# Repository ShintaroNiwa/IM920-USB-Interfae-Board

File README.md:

# IM920c/s/sl USB Interface Board
インタープラン社の無線モジュール、IM920シリーズをUSB Type-CでPCに接続するためのインターフェースボードです。
USBシリアルコンバータICには、部室に余っていたCH340Cを使用します。
対応する無線モジュールについては以下の通りです。
|対応無線モジュール|
|---|
|IM920c|
|IM920s|
|IM920SL|

上記写真ではU2に日本圧着端子製造の20P3.0-JMCS-G-TFを使用しています。

|Reference Name|Parts Name|
|---|---|
|C1|10uF 0603(1608)|
|C2|10uF 0603(1608)|
|C3|0.1uF 0402(1005)|
|C4|0.1uF 0402(1005)|
|C5|0.1uF 0402(1005)|
|D1|LED 0603(1608)|
|D2|LED 0603(1608)|
|D3|LED 0603(1608)|
|D4|LED 0603(1608)|
|J1|USB4105-GF-A|
|R1|5.1kΩ 0402(1005)|
|R2|5.1kΩ 0402(1005)|
|R3|1kΩ 0402(1005)|
|R4|1kΩ 0402(1005)|
|R5|1kΩ 0402(1005)|
|R6|1kΩ 0402(1005)|
|U1|CH340C|
|U2|20Pxx-JMCS-G-TF|
|U3|NCP1117ST33T3G|

※U2の「20Pxx-JMCS-G-TF」はxxスタッキング高さが入ります。

無線モジュールの詳しい使い方については、メーカーのマニュアルを参照してください。

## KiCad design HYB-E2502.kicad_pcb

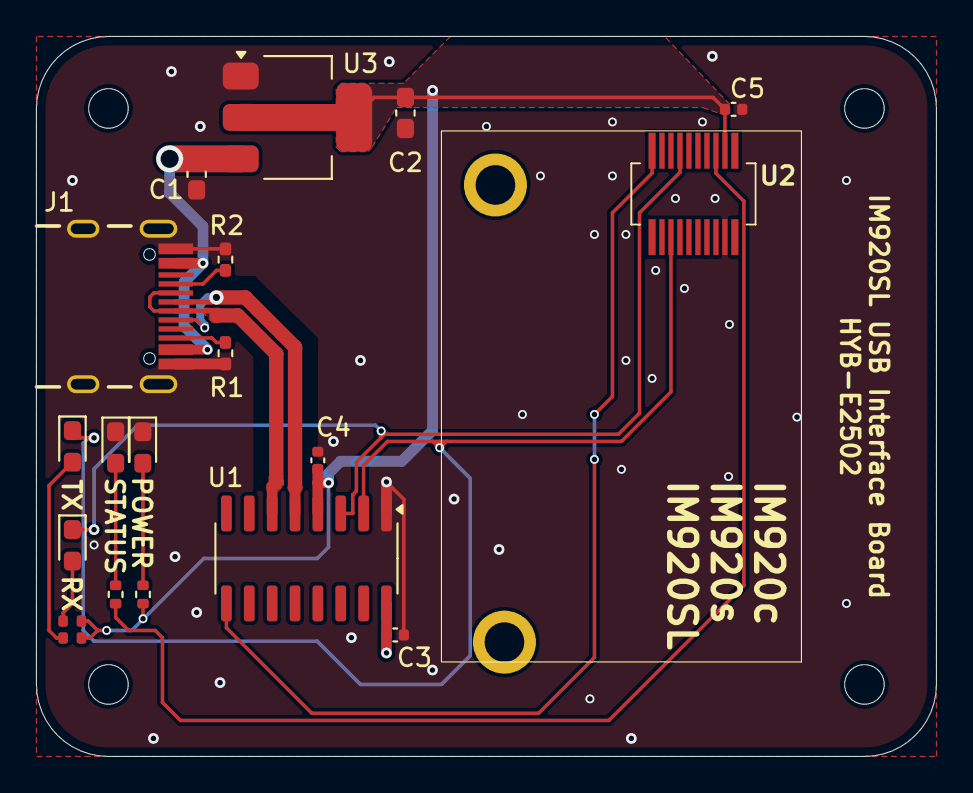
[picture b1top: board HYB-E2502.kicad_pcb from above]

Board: 2 copper layers, 50.0 x 40.0 mm, 23 parts (0 on the bottom side), 15 nets.

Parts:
C1, C2: 10uF; C_0603_1608Metric_Pad1.08x0.95mm_HandSolder
C3, C4, C5: 0.1uF; C_0402_1005Metric
D1, D2, D3, D4: LED; LED_0603_1608Metric_Pad1.05x0.95mm_HandSolder
H1, H2, H3, H4: MountingHole; MountingHole_2.2mm_M2
J1: USB4105-GF-A; GCT_USB4105-GF-A
R1, R2: 5.1k; R_0402_1005Metric_Pad0.72x0.64mm_HandSolder
R3, R4, R5, R6: 1k; R_0402_1005Metric
U1: CH340C; SOP-16_3.9x9.9mm_P1.27mm
U2: IM920SL
U3: NCP1117ST33T3G; SOT-223

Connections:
+3.3V: C2.1, C3.1, C4.1, C5.1, R3.1, R5.1, R6.1, U1.4 (V3), U1.16 (VCC), U2.17 (VCC), U3.2 (OUT), U3.4 (OUT__1)
+5V: C1.1, J1.A4_B9 (VBUS), J1.B4_A9 (VBUS__1), U3.3 (IN)
/USB_DN: J1.A7 (DN1), J1.B7 (DN2), U1.6 (USB_DN)
/USB_DP: J1.A6 (DP1), J1.B6 (DP2), U1.5 (USB_DP)
GND: C1.2, C2.2, C3.2, C4.2, C5.2, D1.1 (K), D2.1 (K), J1.A1_B12 (GND), J1.B1_A12 (GND__1), J1.SH1 (SHELL_GND), J1.SH2 (SHELL_GND__1), J1.SH3 (SHELL_GND__2), J1.SH4 (SHELL_GND__3), R1.1, R2.1, U1.1 (GND), U2.18 (GND), U3.1 (GND)
unnamed: D1.2 (A), R4.2
unnamed: D2.2 (A), R3.2
unnamed: D3.2 (A), R5.2
unnamed: D3.1 (K), U1.3 (RxD), U2.7 (IO7/TxD)
unnamed: D4.2 (A), R6.2
unnamed: D4.1 (K), U1.2 (TxD), U2.6 (IO6/RxD)
unnamed: J1.A5 (CC1), R2.2
unnamed: J1.B5 (CC2), R1.2
unnamed: U1.9 (CTS), U2.1 (IO1/BUSY)
unnamed: R4.1, U2.15 (STATUS)

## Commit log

2025-04-15 Ver 1.0
2025-04-15 Edit/PCB
    TX RX LEDの抵抗の位置を変更
2025-04-15 配線修正
2025-04-23 Remove some unnecessary files
